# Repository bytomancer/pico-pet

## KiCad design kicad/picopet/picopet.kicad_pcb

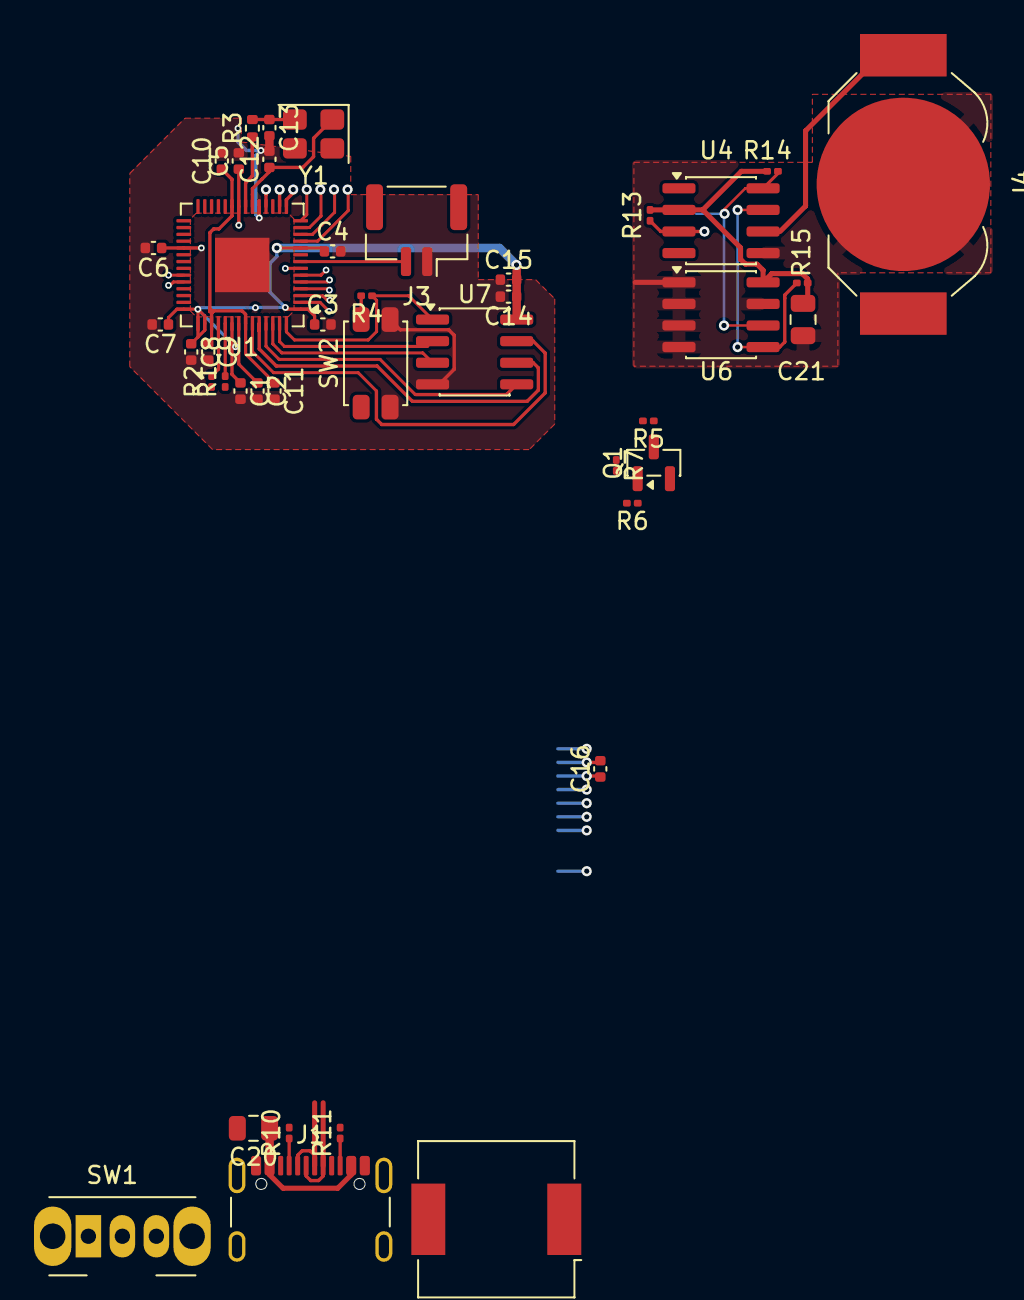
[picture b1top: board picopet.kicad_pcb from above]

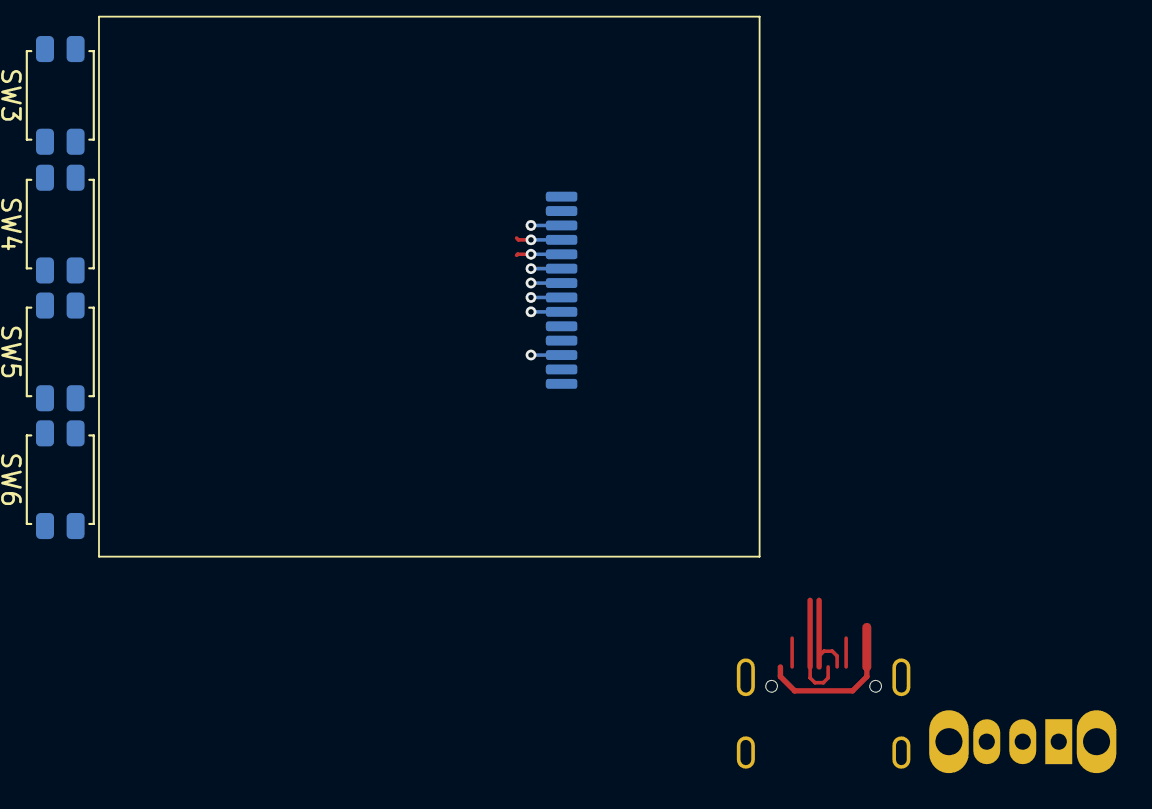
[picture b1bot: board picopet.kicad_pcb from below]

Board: 2 copper layers, 47 parts (5 on the bottom side), 39 nets.

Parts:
BZ1: Buzzer; Buzzer_CUI_CPT-9019S-SMT
C1, C2, C3, C4, C5, C6, C7, C10, C11, C14: 100n; C_0402_1005Metric
C8, C9, C16: 1u; C_0402_1005Metric
C12, C13: 15p; C_0402_1005Metric
C15: 2u2; C_0402_1005Metric
C20, C21: 4.7u; C_0805_2012Metric
J1: USB_C_Receptacle_USB2.0_14P; USB_C_Receptacle_GCT_USB4105-xx-A_16P_TopMnt_Horizontal
J3: PH1.25mm 2P; JST_GH_SM02B-GHS-TB_1x02-1MP_P1.25mm_Horizontal
J4: CR1220 Holder; BatteryHolder_LINX_BAT-HLD-012-SMT
J5: ST7735 LCD; ST7735_P0.8mm
Q1: SS8050; SOT-23
R1, R2: 27; R_0201_0603Metric
R3: 1k; R_0402_1005Metric
R4, R7: 1k; R_0201_0603Metric
R5: 10; R_0201_0603Metric
R6: 10k; R_0201_0603Metric
R10, R11: 5k1; R_0201_0603Metric
R13, R14, R15: 5K1; R_0201_0603Metric
SW1: PWR; SW_Slide_SPDT_Angled_CK_OS102011MA1Q
SW2: BOOTSEL; SW_SPST_EVQP2_MiddlePushTravel_H2.5mm
SW3: Btn0; SW_SPST_EVQP2_MiddlePushTravel_H2.5mm
SW4: Btn1; SW_SPST_EVQP2_MiddlePushTravel_H2.5mm
SW5: Btn2; SW_SPST_EVQP2_MiddlePushTravel_H2.5mm
SW6: Btn3; SW_SPST_EVQP2_MiddlePushTravel_H2.5mm
U1: RP2040; QFN-56-1EP_7x7mm_P0.4mm_EP3.2x3.2mm
U4: DS3231MZ; SOIC-8_3.9x4.9mm_P1.27mm
U6: AT24CS32-SSHM; SOIC-8_3.9x4.9mm_P1.27mm
U7: W25Q32JVSSIQ; SOIC-8_3.9x4.9mm_P1.27mm
Y1: X322512MSB4SI; Crystal_SMD_3225-4Pin_3.2x2.5mm

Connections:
+1V1: C9.1, C10.1, C11.1, U1.23 (DVDD), U1.45 (VREG_VOUT), U1.50 (DVDD)
+3V3: C1.1, C2.1, C3.1, C4.1, C5.1, C6.1, C7.1, C8.1, C14.1, C15.2, C16.2, C21.1, J5.4 (LED+), J5.10 (VCC), J5.11 (IOVCC), R6.2, R13.2, R14.2, R15.2, U1.1 (IOVDD), U1.10 (IOVDD), U1.22 (IOVDD), U1.33 (IOVDD), U1.42 (IOVDD), U1.43 (ADC_AVDD), U1.44 (VREG_IN), U1.48 (USB_VDD), U1.49 (IOVDD), U4.2 (VCC), U6.8 (VCC), U7.8 (VCC)
/QSPI_SCLK: U1.52 (QSPI_SCLK), U7.6 (CLK)
/QSPI_SD0: U1.53 (QSPI_SD0), U7.5 (DI(IO0))
/QSPI_SD1: U1.55 (QSPI_SD1), U7.2 (DO(IO1))
/QSPI_SD2: U1.54 (QSPI_SD2), U7.3 (IO2)
/QSPI_SD3: U1.51 (QSPI_SD3), U7.7 (IO3)
/QSPI_SS: R4.1, U1.56 (QSPI_SS), U7.1 (~CS)
/XIN: C12.1, U1.20 (XIN), Y1.1
/XOUT: R3.1, U1.21 (XOUT)
GND: BZ1.2 (-), C1.2, C2.2, C3.2, C4.2, C5.2, C6.2, C7.2, C8.2, C9.2, C10.2, C11.2, C12.2, C13.2, C14.2, C15.1, C16.1, C20.2, C21.2, J1.A1 (GND), J1.A12 (GND), J1.B1 (GND), J1.B12 (GND), J1.S1 (SHIELD), J3.1, J4.2, J5.2 (GND), J5.5 (GND), J5.13 (GND), Q1.2 (E), R10.2, R11.2, SW2.2, SW3.2, SW4.2, SW5.2, SW6.2, U1.19 (TESTEN), U1.57 (GND), U4.5 (GND), U6.1 (A0), U6.2 (A1), U6.3 (A2), U6.4 (GND), U6.7 (WP), U7.4 (GND)
GPIO0: R15.1, U1.2 (GPIO0), U4.7 (SDA), U6.5 (SDA)
GPIO1: R14.1, U1.3 (GPIO1), U4.8 (SCL), U6.6 (SCL)
GPIO2: SW5.1, U1.4 (GPIO2)
GPIO3: SW6.1, U1.5 (GPIO3)
GPIO4: BZ1.1 (+), U1.6 (GPIO4)
GPIO5: R13.1, U1.7 (GPIO5), U4.3 (~INT/SQW)
GPIO6: J3.2, U1.8 (GPIO6)
GPIO8: J5.7 (A0), U1.11 (GPIO8)
GPIO9: J5.12 (CS), U1.12 (GPIO9)
GPIO10: J5.9 (CLK), U1.13 (GPIO10)
GPIO11: J5.8 (DIN), U1.14 (GPIO11)
GPIO12: J5.6 (~RESET), U1.15 (GPIO12)
GPIO13: R7.1, U1.16 (GPIO13)
GPIO15: SW3.1, U1.18 (GPIO15)
GPIO17: SW4.1, U1.28 (GPIO17)
unnamed: C13.1, R3.2, Y1.2
unnamed: J1.A5 (CC1), R10.1
unnamed: J1.B5 (CC2), R11.1
unnamed: J5.3 (LED-), R5.2
unnamed: Q1.1 (B), R6.1, R7.2
unnamed: Q1.3 (C), R5.1
unnamed: R4.2, SW2.1
unnamed: R2.2, U1.46 (USB_DM)
unnamed: R1.2, U1.47 (USB_DP)
USBC_VDD: C20.1, J1.A4 (VBUS), J1.A9 (VBUS), J1.B4 (VBUS), J1.B9 (VBUS)
USB_D+: J1.A6 (D+), J1.B6 (D+), R1.1
USB_D-: J1.A7 (D-), J1.B7 (D-), R2.1
VCOIN: J4.1, U4.6 (VBAT)

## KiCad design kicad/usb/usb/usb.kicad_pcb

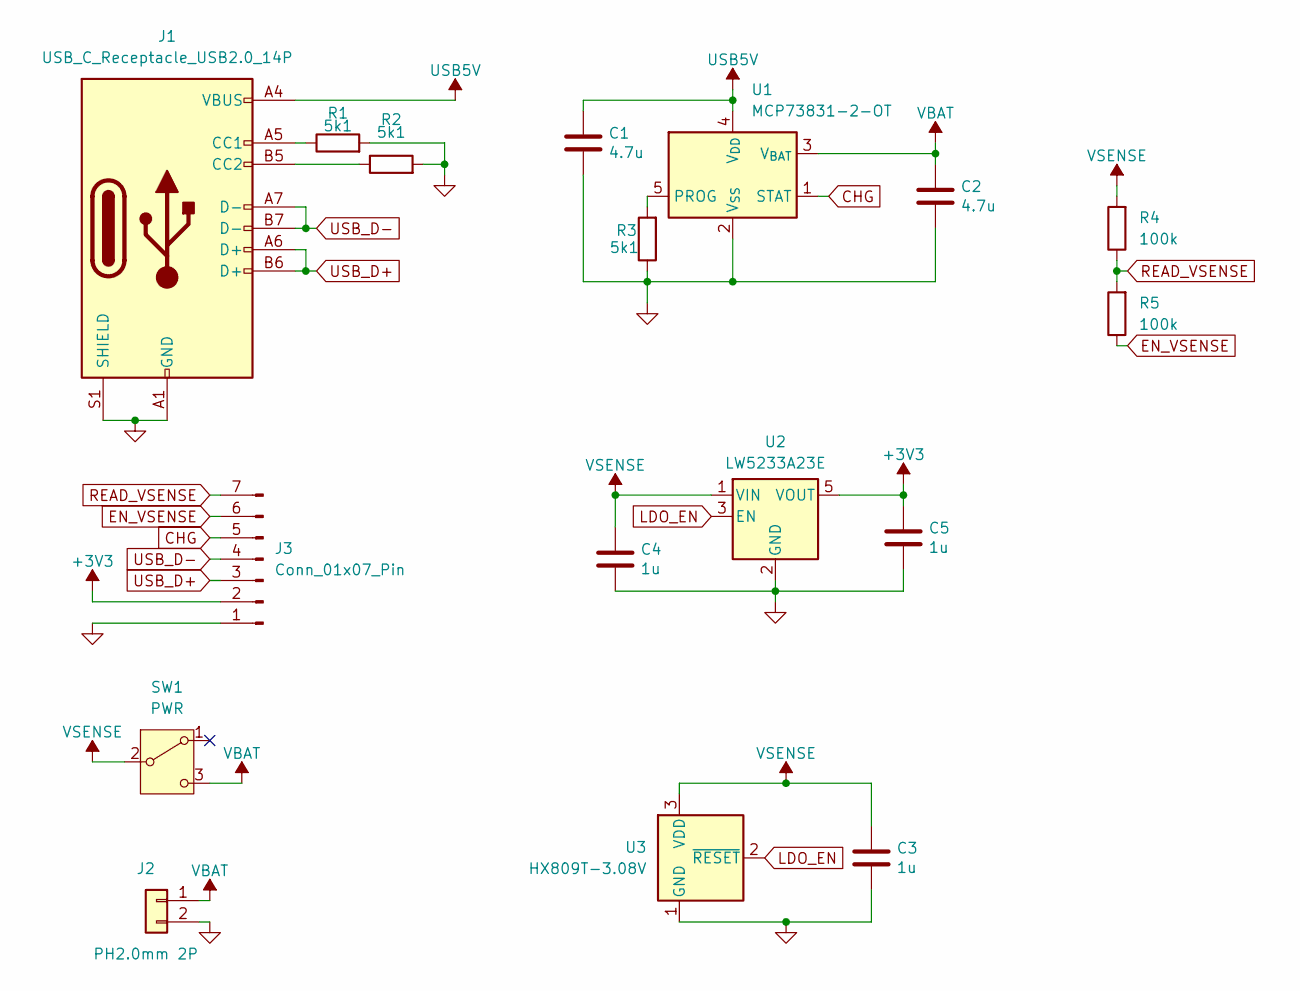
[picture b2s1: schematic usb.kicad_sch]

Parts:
C1, C2: 4.7u; C_0805_2012Metric; LCSC C15850
C3, C4, C5: 1u; C_0805_2012Metric; LCSC C15850
J1: USB_C_Receptacle_USB2.0_14P; USB_C_Receptacle_GCT_USB4105-xx-A_16P_TopMnt_Horizontal
J2: PH2.0mm 2P; JST_PH_S2B-PH-K_1x02_P2.00mm_Horizontal; LCSC C124375
J3: Conn_01x07_Pin; PinHeader_1x07_P2.54mm_Vertical
R1, R2, R3: 5k1; R_0805_2012Metric
R4, R5: 100k; R_0805_2012Metric
SW1: PWR; SW_Slide_SPDT_Angled_CK_OS102011MA1Q
U1: MCP73831-2-OT; SOT-23-5
U2: LW5233A23E; SOT-23-5
U3: HX809T-3.08V; SOT-23

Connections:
+3V3: C5.1, J3.2, U2.5 (VOUT)
CHG: J3.5, U1.1 (STAT)
EN_VSENSE: J3.6, R5.1
GND: C1.2, C2.2, C3.2, C4.2, C5.2, J1.A1 (GND), J1.A12 (GND), J1.B1 (GND), J1.B12 (GND), J1.S1 (SHIELD), J2.2, J3.1, R1.2, R2.2, R3.1, U1.2 (V_{SS}), U2.2 (GND), U3.1 (GND)
LDO_EN: U2.3 (EN), U3.2 (~RESET)
unnamed: J1.A5 (CC1), R1.1
unnamed: J1.B5 (CC2), R2.1
unnamed: R3.2, U1.5 (PROG)
READ_VSENSE: J3.7, R4.1, R5.2
USB5V: C1.1, J1.A4 (VBUS), J1.A9 (VBUS), J1.B4 (VBUS), J1.B9 (VBUS), U1.4 (V_{DD})
USB_D+: J1.A6 (D+), J1.B6 (D+), J3.3
USB_D-: J1.A7 (D-), J1.B7 (D-), J3.4
VBAT: C2.1, J2.1, SW1.3 (C), U1.3 (V_{BAT})
VSENSE: C3.1, C4.1, R4.2, SW1.2 (B), U2.1 (VIN), U3.3 (VDD)

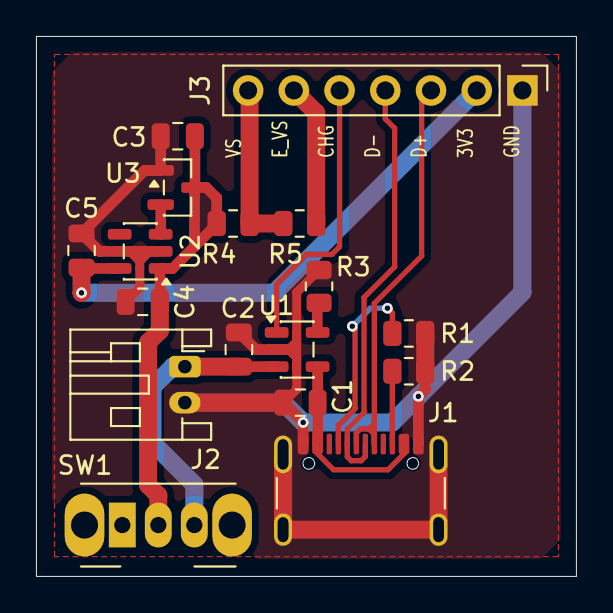
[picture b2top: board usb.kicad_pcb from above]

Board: 2 copper layers, 30.0 x 30.0 mm, 17 parts (0 on the bottom side), 14 nets.

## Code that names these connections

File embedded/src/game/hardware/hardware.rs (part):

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
type DisplaySdi = rp2040_hal::Spi<rp2040_hal::spi::Enabled, pac::SPI1, 8>;
type DisplayDc = rp2040_hal::gpio::Pin<
    rp2040_hal::gpio::bank0::Gpio8,
    rp2040_hal::gpio::Output<rp2040_hal::gpio::PushPull>,
>;
type DisplayRst = rp2040_hal::gpio::Pin<
    rp2040_hal::gpio::bank0::Gpio12,
    rp2040_hal::gpio::Output<rp2040_hal::gpio::PushPull>,
>;

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    rp2040_hal::gpio::Input<rp2040_hal::gpio::PullUp>,
>;
type Key1Pin = rp2040_hal::gpio::Pin<
    rp2040_hal::gpio::bank0::Gpio17,
    rp2040_hal::gpio::Input<rp2040_hal::gpio::PullUp>,
>;
type Key2Pin = rp2040_hal::gpio::Pin<
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    rp2040_hal::gpio::Input<rp2040_hal::gpio::PullUp>,
>;
type HzPin = rp2040_hal::gpio::Pin<
    rp2040_hal::gpio::bank0::Gpio2,
    rp2040_hal::gpio::Input<rp2040_hal::gpio::PullUp>,
>;
type ChargeIndicatorPin = rp2040_hal::gpio::Pin<
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>;

type VibePin = rp2040_hal::gpio::Pin<
    rp2040_hal::gpio::bank0::Gpio3,
    rp2040_hal::gpio::Output<rp2040_hal::gpio::PushPull>,
>;

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    pac::I2C0,
    (
        rp2040_hal::gpio::Pin<
            rp2040_hal::gpio::bank0::Gpio0,
            rp2040_hal::gpio::Function<rp2040_hal::gpio::I2C>,
        >,
        rp2040_hal::gpio::Pin<
            rp2040_hal::gpio::bank0::Gpio1,
            rp2040_hal::gpio::Function<rp2040_hal::gpio::I2C>,
        >,
    ),
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    pub fifo_ptr: *mut SioFifo,
    pub i2c_bus: I2CBus,
    pub adc: Adc,
    pub vsense_pin: Adc0Pin,
    pub vsense_enable_pin: VsenseEnablePin,
    pub nvm_addr: u8,
}
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
            let buzzer_channel_ptr =
                &mut (*buzzer_pwm_slice_ptr).channel_a as *mut BuzzerPinChannel;
            (*buzzer_channel_ptr).output_to(pins.gpio4);
            (*buzzer_channel_ptr).enable();
            (*buzzer_channel_ptr).set_duty(0);

            let buzzer_channel_neg_ptr =
                &mut (*buzzer_pwm_slice_ptr).channel_b as *mut BuzzerNegPinChannel;
            (*buzzer_channel_neg_ptr).output_to(pins.gpio5);
            (*buzzer_channel_neg_ptr).enable();
            (*buzzer_channel_neg_ptr).set_duty(0);

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            // Output channel B on PWM6 to GPIO 13
            let backlight_channel_ptr = &mut pwm6.channel_b as *mut LcdBlPinChannel;
            // disable backlight ASAP to hide boot artifacts
            (*backlight_channel_ptr).output_to(pins.gpio13);
            (*backlight_channel_ptr).enable();
            (*backlight_channel_ptr).set_duty(0);

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            (*buzzer_pwm_slice_ptr).enable();

            let key0: Key0Pin = pins.gpio16.into_pull_up_input();
            let key1: Key1Pin = pins.gpio17.into_pull_up_input();
            let key2: Key2Pin = pins.gpio18.into_pull_up_input();
            let key3: Key3Pin = pins.gpio19.into_pull_up_input();
            let key5: HzPin = pins.gpio2.into_pull_up_input();
            let chg_ind_pin: ChargeIndicatorPin = pins.gpio27.into_pull_up_input();

            let mut vsense_enable_pin = pins.gpio28.into_push_pull_output();
            vsense_enable_pin.set_low().unwrap();

            let adc: Adc = Adc::new(pac.ADC, &mut pac.RESETS);
            let vsense_pin = pins.gpio26.into_floating_input();

            let mut vibe = pins.gpio3.into_push_pull_output();
            vibe.set_low().unwrap();

            let sys_freq = clocks.system_clock.freq().to_Hz();
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
            let (mut _pio, _sm0, _, _, _) = pac.PIO0.split(&mut pac.RESETS);

            let lcd_dc = pins.gpio8.into_push_pull_output();
            let mut _lcd_cs = pins.gpio9.into_mode::<rp2040_hal::gpio::FunctionSpi>();
            let mut _lcd_clk = pins.gpio10.into_mode::<rp2040_hal::gpio::FunctionSpi>();
            let mut _lcd_mosi = pins.gpio11.into_mode::<rp2040_hal::gpio::FunctionSpi>();
            let lcd_rst = pins
                .gpio12
                .into_push_pull_output_in_state(rp2040_hal::gpio::PinState::High);

            let spi = rp2040_hal::Spi::<_, _, 8>::new(pac.SPI1);
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                .clear(Rgb565::BLACK)
                .expect("Could not initialize display");

            let sda_pin = pins.gpio0.into_mode::<rp2040_hal::gpio::FunctionI2C>();
            let scl_pin = pins.gpio1.into_mode::<rp2040_hal::gpio::FunctionI2C>();

            let mut i2c_bus: I2CBus = rp2040_hal::I2C::i2c0(
                pac.I2C0,
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                fifo_ptr,
                i2c_bus,
                adc,
                vsense_pin,
                vsense_enable_pin,
                nvm_addr,
            };
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                rp2040_hal::gpio::bank0::Gpio26,
                rp2040_hal::gpio::Input<rp2040_hal::gpio::Floating>,
            >,
        >>::read(&mut self.adc, &mut self.vsense_pin)
        .unwrap_or(0)
    }

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
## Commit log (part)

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2026-03-23 Getting rid of the vdiv switch after some testing
2026-03-25 New notes on feeding
